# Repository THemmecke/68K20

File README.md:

# 68K20
68020 Board EAGLE/VHDL

This repository contains EAGLE and VHDL sources for a 68020 based SBC. The ECB based SBC provides a 68020 cpu, 68881/2 FPU, full 32 bit address and databus, 4MB SRAM and 512KB FLASH on board, 12(C)887 RTC.
It can be used with the GDP-FPGA (https://github.com/THemmecke/GDPFPGAII) to build a complete microcomputer system.

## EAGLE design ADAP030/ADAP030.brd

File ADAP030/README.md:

# 68030 Adapter

With this adapter plugged into the 68020 socket of the CPU68K20 the card upgrades to an CPU68K30 with 

  - 68030/33Mhz CPU (tested)
  - MMU (!)
  - 68882 FPU

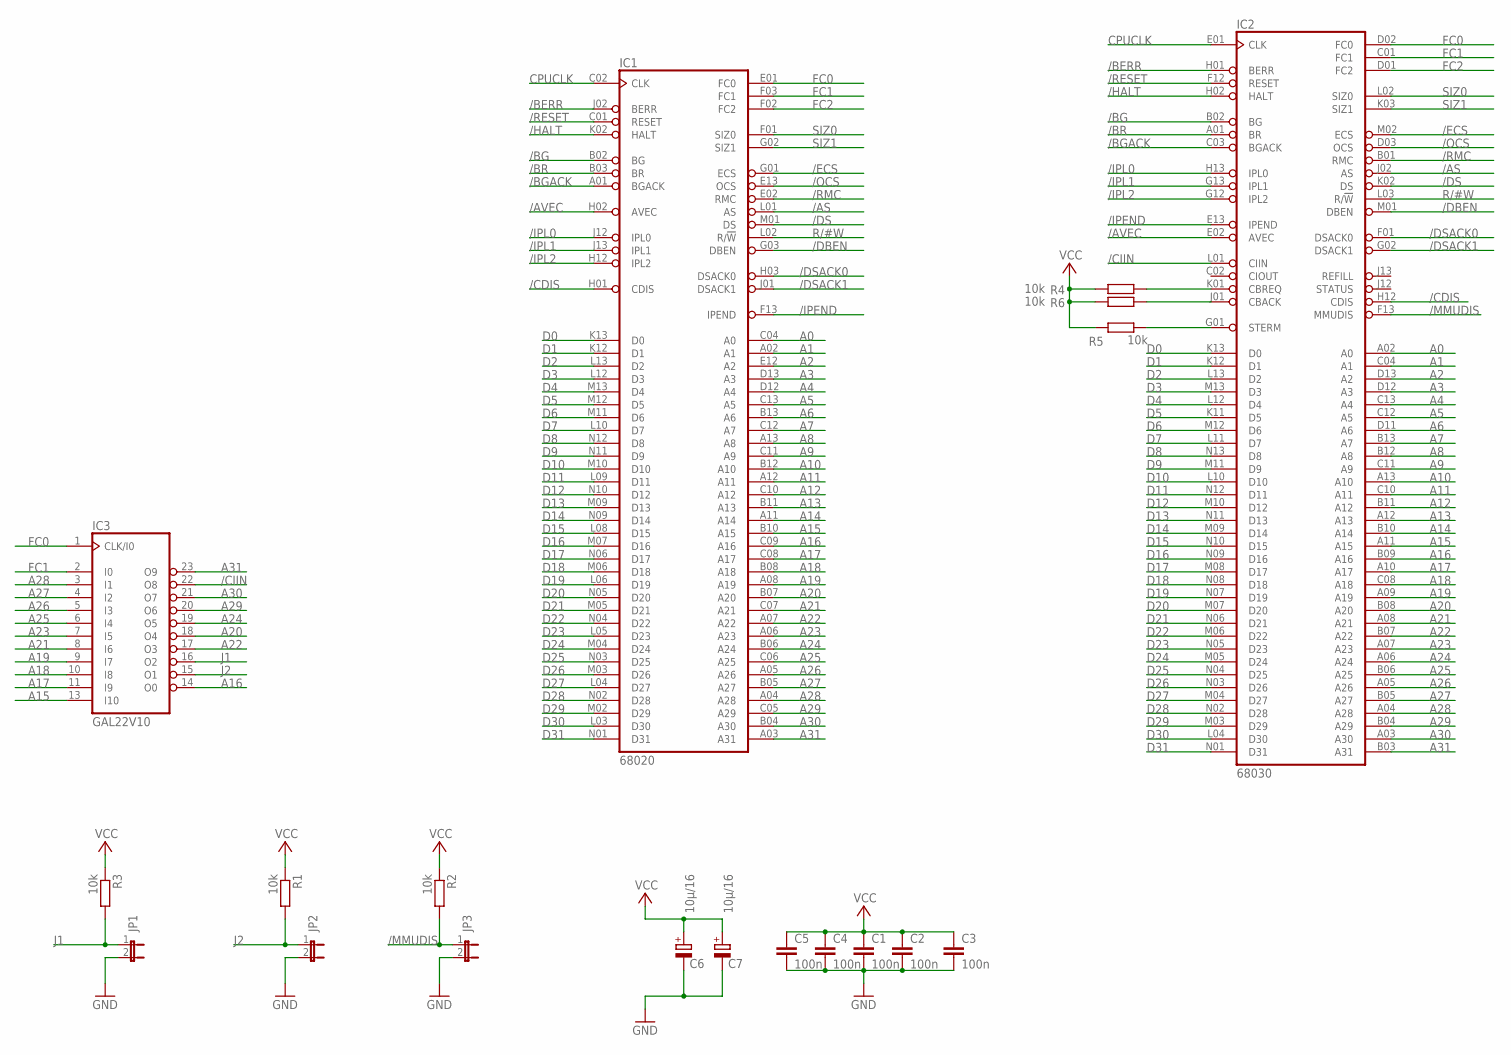
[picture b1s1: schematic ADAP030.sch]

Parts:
C1, C2, C3, C4, C5: 100n; C0603K
C6, C7: 10µ/16; SMC_C
IC1: 68020; MPGA114
IC2: 68030; MPGA128
IC3: GAL22V10; DIL24-3
JP1, JP2, JP3: JP1E; JP1
R1, R2, R3, R4, R5, R6: 10k; M0805

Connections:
/AS: IC1.L01 (AS), IC2.J02 (AS)
/AVEC: IC1.H02 (AVEC), IC2.E02 (AVEC)
/BERR: IC1.J02 (BERR), IC2.H01 (BERR)
/BG: IC1.B02 (BG), IC2.B02 (BG)
/BGACK: IC1.A01 (BGACK), IC2.C03 (BGACK)
/BR: IC1.B03 (BR), IC2.A01 (BR)
/CDIS: IC1.H01 (CDIS), IC2.H12 (CDIS)
/CIIN: IC2.L01 (CIIN), IC3.22 (O8)
/DBEN: IC1.G03 (DBEN), IC2.M01 (DBEN)
/DS: IC1.M01 (DS), IC2.K02 (DS)
/DSACK0: IC1.H03 (DSACK0), IC2.F01 (DSACK0)
/DSACK1: IC1.J01 (DSACK1), IC2.G02 (DSACK1)
/ECS: IC1.G01 (ECS), IC2.M02 (ECS)
/HALT: IC1.K02 (HALT), IC2.H02 (HALT)
/IPEND: IC1.F13 (IPEND), IC2.E13 (IPEND)
/IPL0: IC1.J12 (IPL0), IC2.H13 (IPL0)
/IPL1: IC1.J13 (IPL1), IC2.G13 (IPL1)
/IPL2: IC1.H12 (IPL2), IC2.G12 (IPL2)
/MMUDIS: IC2.F13 (MMUDIS), JP3.1, R2.2
/OCS: IC1.E13 (OCS), IC2.D03 (OCS)
/RESET: IC1.C01 (RESET), IC2.F12 (RESET)
/RMC: IC1.E02 (RMC), IC2.B01 (RMC)
A0: IC1.C04 (A0), IC2.A02 (A0)
A1: IC1.A02 (A1), IC2.C04 (A1)
A2: IC1.E12 (A2), IC2.D13 (A2)
A3: IC1.D13 (A3), IC2.D12 (A3)
A4: IC1.D12 (A4), IC2.C13 (A4)
A5: IC1.C13 (A5), IC2.C12 (A5)
A6: IC1.B13 (A6), IC2.D11 (A6)
A7: IC1.C12 (A7), IC2.B13 (A7)
A8: IC1.A13 (A8), IC2.B12 (A8)
A9: IC1.C11 (A9), IC2.C11 (A9)
A10: IC1.B12 (A10), IC2.A13 (A10)
A11: IC1.A12 (A11), IC2.C10 (A11)
A12: IC1.C10 (A12), IC2.B11 (A12)
A13: IC1.B11 (A13), IC2.A12 (A13)
A14: IC1.A11 (A14), IC2.B10 (A14)
A15: IC1.B10 (A15), IC2.A11 (A15), IC3.13 (I10)
A16: IC1.C09 (A16), IC2.B09 (A16), IC3.14 (O0)
A17: IC1.C08 (A17), IC2.A10 (A17), IC3.11 (I9)
A18: IC1.B08 (A18), IC2.C08 (A18), IC3.10 (I8)
A19: IC1.A08 (A19), IC2.A09 (A19), IC3.9 (I7)
A20: IC1.B07 (A20), IC2.B08 (A20), IC3.18 (O4)
A21: IC1.C07 (A21), IC2.A08 (A21), IC3.8 (I6)
A22: IC1.A07 (A22), IC2.B07 (A22), IC3.17 (O3)
A23: IC1.A06 (A23), IC2.A07 (A23), IC3.7 (I5)
A24: IC1.B06 (A24), IC2.A06 (A24), IC3.19 (O5)
A25: IC1.C06 (A25), IC2.B06 (A25), IC3.6 (I4)
A26: IC1.A05 (A26), IC2.A05 (A26), IC3.5 (I3)
A27: IC1.B05 (A27), IC2.B05 (A27), IC3.4 (I2)
A28: IC1.A04 (A28), IC2.A04 (A28), IC3.3 (I1)
A29: IC1.C05 (A29), IC2.B04 (A29), IC3.20 (O6)
A30: IC1.B04 (A30), IC2.A03 (A30), IC3.21 (O7)
A31: IC1.A03 (A31), IC2.B03 (A31), IC3.23 (O9)
CBACK: IC2.J01 (CBACK), R6.2
CNREQ: IC2.K01 (CBREQ), R4.2
CPUCLK: IC1.C02 (CLK), IC2.E01 (CLK)
D0: IC1.K13 (D0), IC2.K13 (D0)
D1: IC1.K12 (D1), IC2.K12 (D1)
D2: IC1.L13 (D2), IC2.L13 (D2)
D3: IC1.L12 (D3), IC2.M13 (D3)
D4: IC1.M13 (D4), IC2.L12 (D4)
D5: IC1.M12 (D5), IC2.K11 (D5)
D6: IC1.M11 (D6), IC2.M12 (D6)
D7: IC1.L10 (D7), IC2.L11 (D7)
D8: IC1.N12 (D8), IC2.N13 (D8)
D9: IC1.N11 (D9), IC2.M11 (D9)
D10: IC1.M10 (D10), IC2.L10 (D10)
D11: IC1.L09 (D11), IC2.N12 (D11)
D12: IC1.N10 (D12), IC2.M10 (D12)
D13: IC1.M09 (D13), IC2.N11 (D13)
D14: IC1.N09 (D14), IC2.M09 (D14)
D15: IC1.L08 (D15), IC2.N10 (D15)
D16: IC1.M07 (D16), IC2.N09 (D16)
D17: IC1.N06 (D17), IC2.M08 (D17)
D18: IC1.M06 (D18), IC2.N08 (D18)
D19: IC1.L06 (D19), IC2.N07 (D19)
D20: IC1.N05 (D20), IC2.M07 (D20)
D21: IC1.M05 (D21), IC2.N06 (D21)
D22: IC1.N04 (D22), IC2.M06 (D22)
D23: IC1.L05 (D23), IC2.N05 (D23)
D24: IC1.M04 (D24), IC2.M05 (D24)
D25: IC1.N03 (D25), IC2.N04 (D25)
D26: IC1.M03 (D26), IC2.N03 (D26)
D27: IC1.L04 (D27), IC2.M04 (D27)
D28: IC1.N02 (D28), IC2.N02 (D28)
D29: IC1.M02 (D29), IC2.M03 (D29)
D30: IC1.L03 (D30), IC2.L04 (D30)
D31: IC1.N01 (D31), IC2.N01 (D31)
FC0: IC1.E01 (FC0), IC2.D02 (FC0), IC3.1 (CLK/I0)
FC1: IC1.F03 (FC1), IC2.C01 (FC1), IC3.2 (I0)
FC2: IC1.F02 (FC2), IC2.D01 (FC2)
GND: C1.2, C2.2, C3.2, C4.2, C5.2, C6.-, C7.-, IC1.A10 (GND), IC1.B01 (GND), IC1.B09 (GND), IC1.C03 (GND), IC1.F12 (GND), IC1.G12 (GND), IC1.H13 (GND), IC1.J03 (GND), IC1.K01 (GND), IC1.K03 (GND), IC1.L07 (GND), IC1.L11 (GND), IC1.N07 (GND), IC2.C05 (GND), IC2.C07 (GND), IC2.C09 (GND), IC2.E03 (GND), IC2.E11 (GND), IC2.F03 (GND), IC2.G03 (GND), IC2.G11 (GND), IC2.J03 (GND), IC2.J11 (GND), IC2.L05 (GND), IC2.L07 (GND), IC2.L08 (GND), IC2.L09 (GND), IC3.12 (GND), JP1.2, JP2.2, JP3.2
J1: IC3.16 (O2), JP1.1, R3.2
J2: IC3.15 (O1), JP2.1, R1.2
R/#W: IC1.L02 (R/!W), IC2.L03 (R/!W)
SIZ0: IC1.F01 (SIZ0), IC2.L02 (SIZ0)
SIZ1: IC1.G02 (SIZ1), IC2.K03 (SIZ1)
STERM: IC2.G01 (STERM), R5.2
VCC: C1.1, C2.1, C3.1, C4.1, C5.1, C6.+, C7.+, IC1.A09 (VCC), IC1.D01 (VCC), IC1.D02 (VCC), IC1.D03 (VCC), IC1.E03 (VCC), IC1.G11 (VCC), IC1.G13 (VCC), IC1.M08 (VCC), IC1.N08 (VCC), IC1.N13 (VCC), IC2.C06 (VCC), IC2.D04 (VCC), IC2.D10 (VCC), IC2.F02 (VCC), IC2.F11 (VCC), IC2.H03 (VCC), IC2.H11 (VCC), IC2.K04 (VCC), IC2.K10 (VCC), IC2.L06 (VCC), IC3.24 (VCC), R1.1, R2.1, R3.1, R4.1, R5.1, R6.1

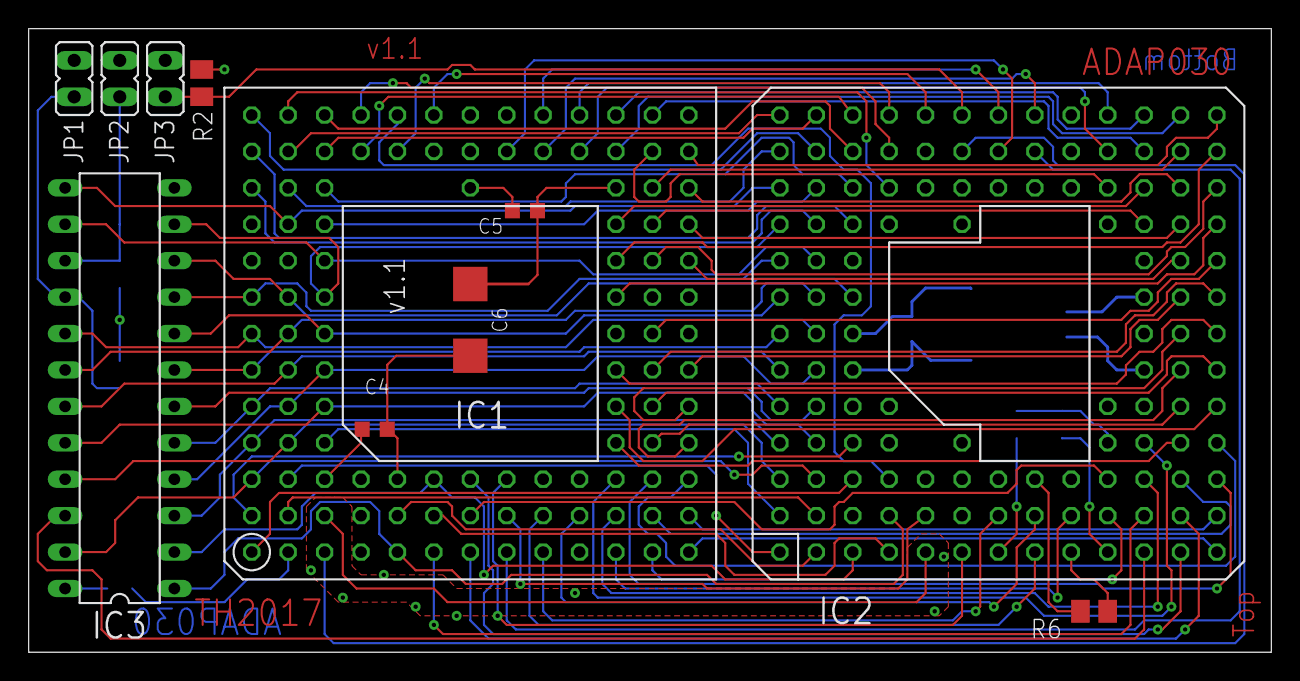
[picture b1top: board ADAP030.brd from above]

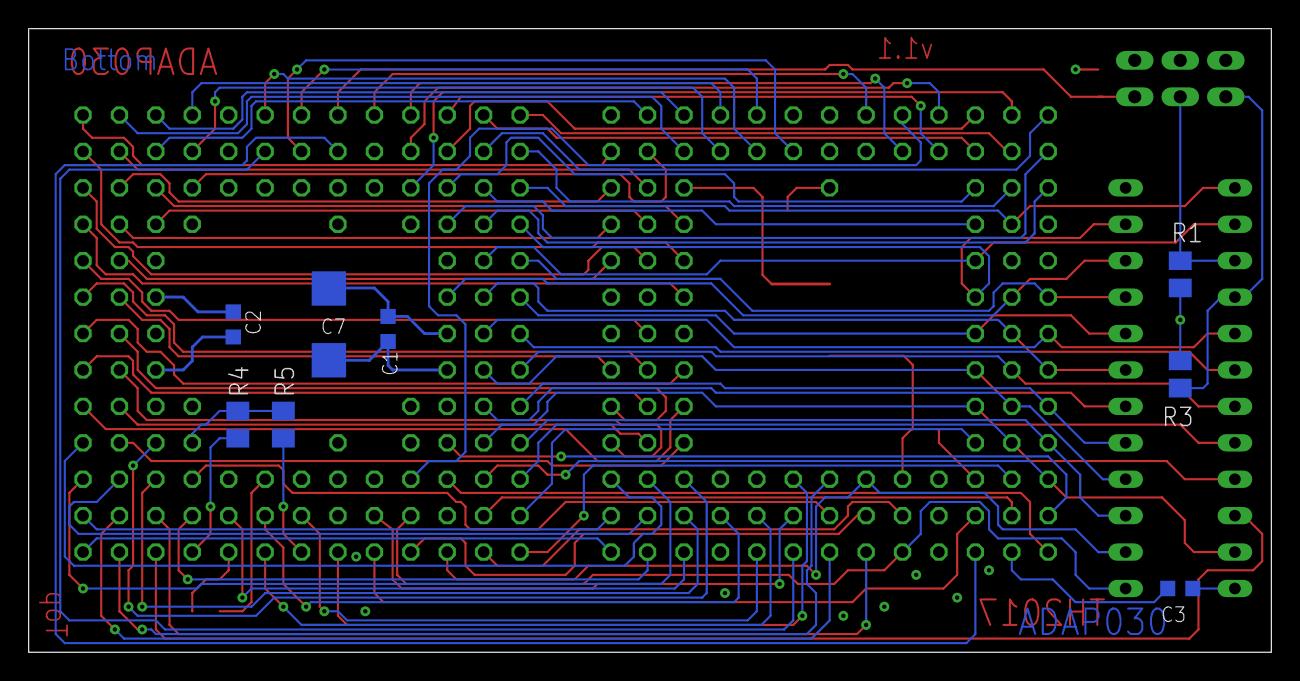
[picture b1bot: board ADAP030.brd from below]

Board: 4 copper layers, 86.7 x 43.5 mm, 19 parts (8 on the bottom side), 100 nets.

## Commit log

2018-01-30 Added GP with Loader
2019-04-30 68030 adapter card
2019-04-30 Update ADAP030
2019-05-01 CBACK
2019-05-08 JADOS image
2019-05-08 foramtting
2019-05-08 fomatting
2019-05-08 formatting
2021-07-22 SDIO.ASM
